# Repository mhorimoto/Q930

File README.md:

# Q930

TWE ARIA を用いた加速度センサ

https://mono-wireless.com/jp/products/twelite-aria/index.html

これと

https://www.digikey.jp/ja/products/detail/sparkfun-electronics/SEN-14480/8032538

これを使用する。

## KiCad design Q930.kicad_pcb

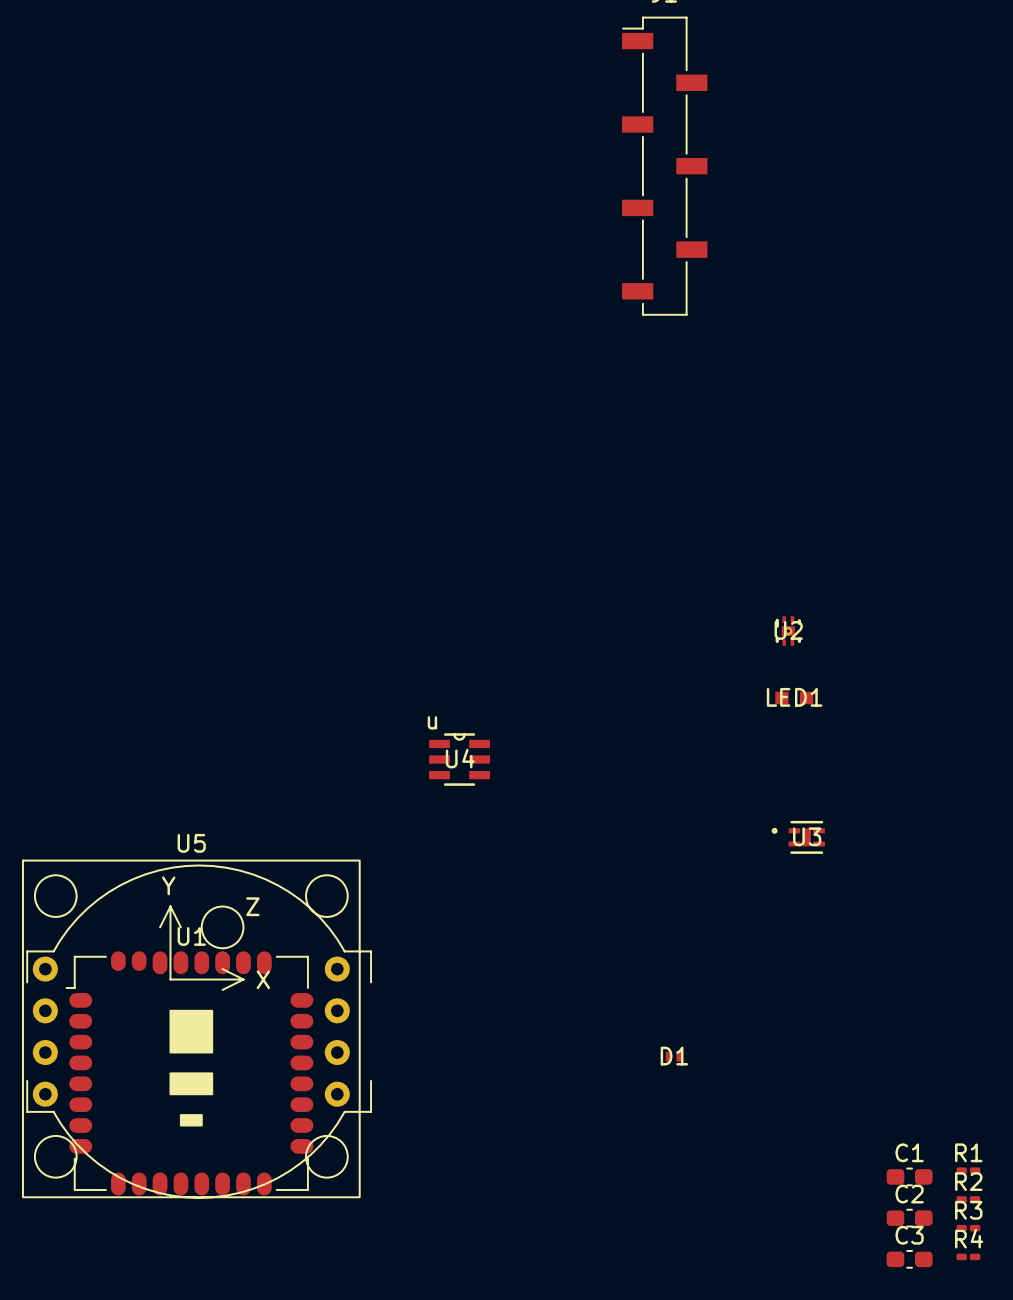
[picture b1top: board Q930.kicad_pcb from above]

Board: 2 copper layers, 16 parts (0 on the bottom side), 18 nets, no tracks yet.

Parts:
BT1: CR2032; BatteryHolder_MPD_BC2003_1x2032
C1, C2, C3: 0.1u; C_0603_1608Metric_Pad1.08x0.95mm_HandSolder
D1: 1SS387CT_L3FT; CST2_TOS
J1: 7Pin; PinSocket_1x07_P2.54mm_Vertical_SMD_Pin1Left
LED1: LB Q39E-L2OO-35-1; LED_LBQ39E_OSR
R1, R2: 3.3k; R_0201_0603Metric_Pad0.64x0.40mm_HandSolder
R3: 470; R_0201_0603Metric_Pad0.64x0.40mm_HandSolder
R4: 27k; R_0201_0603Metric_Pad0.64x0.40mm_HandSolder
U1: MW-R-WX; MonoWireless_TWE-L-WX
U2: DRV5032FDDMRR; DMR0004A
U3: SHT40I-AD1B-R2; SHT40I_SEN
U4: TPL5010DDCR; DDC0006A_L
U5: SEN-14480

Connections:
+3V0: BT1.1 (+), C1.1, C2.2, C3.1, J1.6, R1.1, R2.1, R3.1, R4.1, U1.5 (VCC), U2.1 (VCC), U3.3 (VDD), U4.1 (VDD), U5.6 (Vcc)
/INT1: U1.24 (DIO0/AI2), U5.4 (INT1)
/INT2: U1.25 (DIO1/AI4), U5.3 (INT2)
/LED: LED1.1, U1.7 (DIO5/PWM1)
/RX: J1.4, U1.9 (DIO7/RX)
/SNS_OUT1: U1.18 (DIO16/DI4), U2.4 (OUT)
/SNS_OUT2: U1.10 (DIO8/PWM4), U2.3 (OUT2)
/SPIMISO: J1.3, U1.2 (DO1/PWM3)
/TX: J1.2, U1.8 (DIO6/TX)
/WDTOUT: U1.15 (DIO13/DI2), U4.4 (DONE)
GND: C1.2, C2.1, C3.2, J1.1, U1.20 (GND), U1.28 (GND), U1.30 (GND), U1.31 (GND), U1.32 (GND), U2.2 (GND), U3.4 (VSS), U4.2 (GND), U5.5 (GND)
unnamed: J1.7, U1.13 (DIO12/DI1)
unnamed: LED1.2, R3.2
unnamed: R4.2, U4.3 (DELAY_M_RST)
unnamed: D1.1, U4.6 (RST_N)
RESETN: D1.2, J1.5, U1.21 (~RESET)
W_SCL: R1.2, U1.14 (DIO14/SCL), U3.2 (SCL), U5.8 (SCL)
W_SDA: R2.2, U1.17 (DIO15/SDA), U3.1 (SDA), U5.7 (SDA)

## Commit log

2024-01-26 continue
2024-01-30 シンボル整形
2025-05-21 KiCAD 8対応
